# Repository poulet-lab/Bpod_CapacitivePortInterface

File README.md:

# Capacitive Port Interface for Bpod State Machine

A drop-in replacement for the [regular port interface](https://www.sanworks.io/shop/viewproduct?productID=1004) enabling for capacitive sensing of lick events. Connect a metal lickspout with a short piece of wire to the SNS port of the interface. Baseline calibration will be performed upon power-on - it can be triggered by briefly unplugging the port interface's RJ45 cable from the Bpod's behavior port once everything is in place.

## Bill of Materials
| Item     | Vendor    | Qty | Part Number                                                                                                                        | Description                 |
| :------- | :------   | :-: | :--------------------------------------------------------------------------------------------------------------------------------- | :-------------------------  |
| C1       | Digi-Key  |  1  | [CC1206JRX7R9BB682-ND](https://www.digikey.com/products/en?keywords=CC1206JRX7R9BB682-ND)                                                        | 6.8 nF capacitor (1206)      |
| C2, C3   | Digi-Key  |  2  | [311-1179-2-ND](https://www.digikey.com/products/en?keywords=311-1179-2-ND)                                                        | 100 nF capacitor (1206)     |
| IC1      | Digi-Key  |  1  | [AT42QT1011-TSHRTR-ND](https://www.digikey.com/products/en?keywords=AT42QT1011-TSHRTR-ND)                                          | touch sensor IC             |
| R1       | Digi-Key  |  1  | [13-RC1206FR-1010KLTR-ND](https://www.digikey.com/products/en?keywords=13-RC1206FR-1010KLTR-ND)                                    | 10k ohm resistor (1206)     |
| R2       | Digi-Key  |  1  | [13-RC1206FR-1010RLTR-ND](https://www.digikey.com/products/en?keywords=13-RC1206FR-1010RLTR-ND)                                    | 10 ohm resistor (1206)      |
|          | Digi-Key  |  1  | [3362P-501LF-ND](https://www.digikey.com/products/en?keywords=3362P-501LF-ND)                                                      | 500 ohm trimpot             |
|          | Digi-Key  |  1  | [277-1721-ND](https://www.digikey.com/products/en?keywords=277-1721-ND)                                                            | 2 pos screw terminal	    |
|          | Digi-Key  |  1  | [277-1736-ND](https://www.digikey.com/products/en?keywords=277-1736-ND)                                                            | 4 pos screw terminal	    |
|          | Digi-Key  |  1  | [A31413-ND](https://www.digikey.com/products/en?keywords=A31413-ND)                                                                | Ethernet jack               |
|          | Lee Valve |  1  | [LHDA1231115H](https://www.theleeco.com/products/electro-fluidic-systems/solenoid-valves/control-valves/lhd-series/3-port/ported/) | Solenoid valve              |

The above BOM is for the ```no_user``` version of the PCB. If you want to access the 
extra two lines of the RJ45 connector (like we do at Poulet-Lab) use the respective version of the PCB (```PortBreakoutCapacitive_r*.brd```) and swap the 4 position screw terminal for a 6 position screw terminal ([277-1738-ND](https://www.digikey.com/products/en?keywords=277-1738-ND)).

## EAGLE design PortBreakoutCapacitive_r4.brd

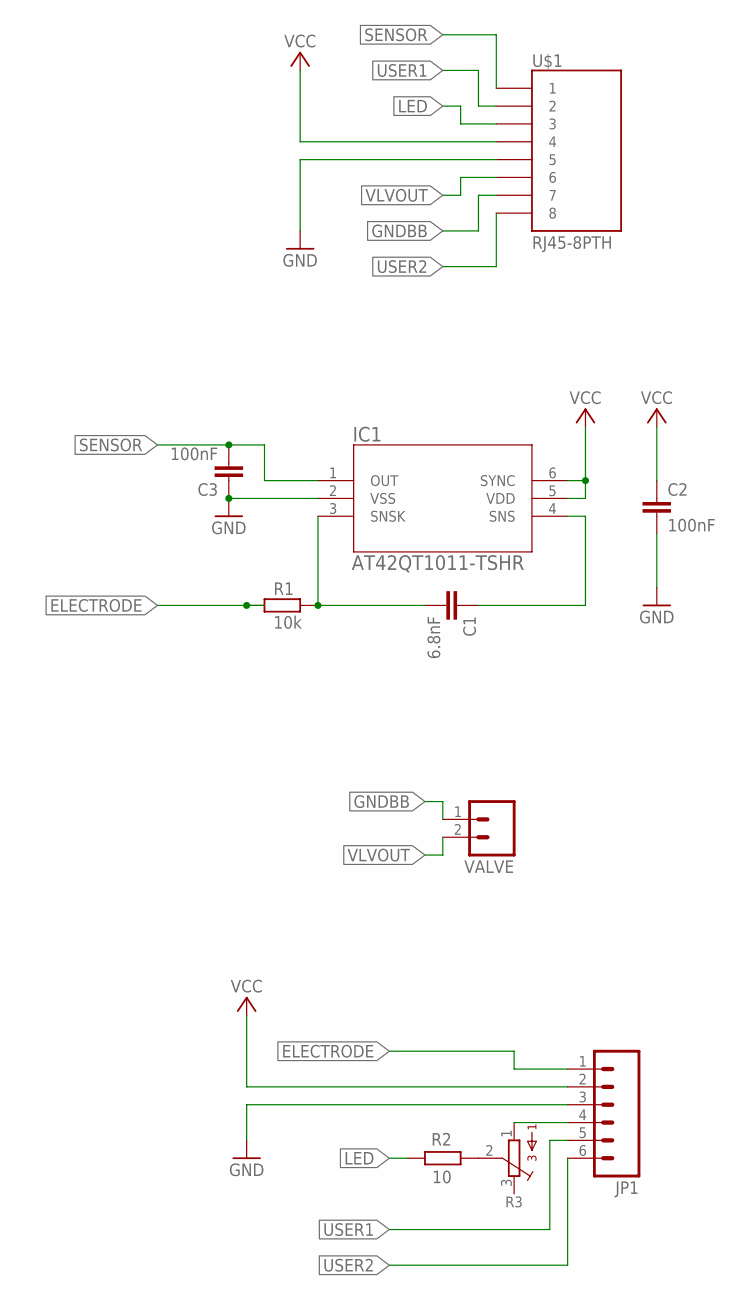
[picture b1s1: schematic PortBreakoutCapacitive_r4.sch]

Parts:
C1: 6.8nF; C1206
C2, C3: 100nF; C1206
IC1: AT42QT1011-TSHR; 6ST1_ATM
JP1: M063.5MM-6; SCREWTERMINAL-3.5MM-6
R1: 10k; R1206
R2: 10; R1206
R3: 3362R
U$1: RJ45-8PTH; RJ45-8
VALVE: M023.5MM_LOCK; SCREWTERMINAL-3.5MM-2_LOCK

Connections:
ELECTRODE: JP1.1, R1.1
GND: C2.2, C3.1, IC1.2 (VSS), JP1.3, U$1.5
GNDBB: U$1.7, VALVE.1
LED: R2.2, U$1.3
unnamed: R2.1, R3.2
unnamed: JP1.4, R3.1
SENSOR: C3.2, IC1.1 (OUT), U$1.1
SNS: C1.1, IC1.4 (SNS)
SNSK: C1.2, IC1.3 (SNSK), R1.2
USER1: JP1.5, U$1.2
USER2: JP1.6, U$1.8
VCC: C2.1, IC1.5 (VDD), IC1.6 (SYNC), JP1.2, U$1.4
VLVOUT: U$1.6, VALVE.2

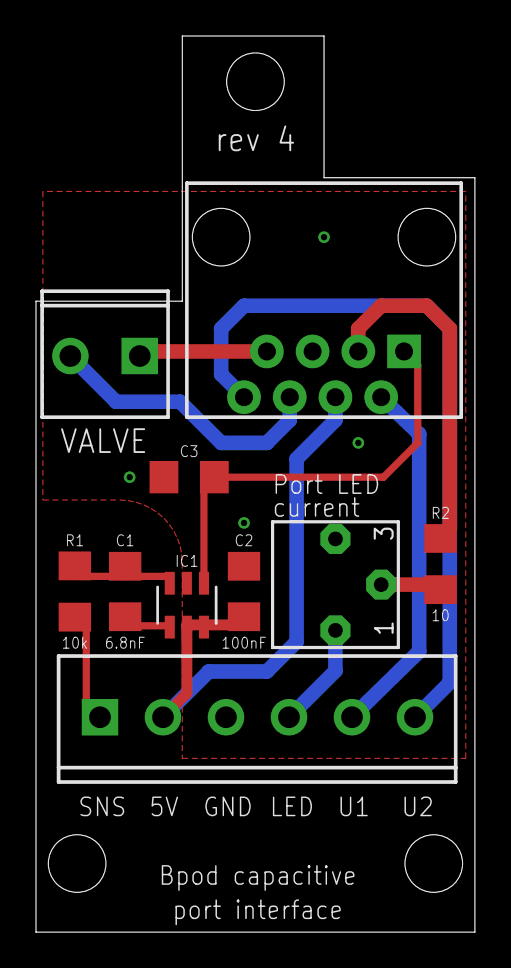
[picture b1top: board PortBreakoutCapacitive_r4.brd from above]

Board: 2 copper layers, 24.4 x 49.8 mm, 10 parts (0 on the bottom side), 13 nets.

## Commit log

2021-04-01 minor adjustments
2021-06-29 revision 2
2022-03-11 Removed transistor Q1
2022-03-11 minor clean-up
2022-03-11 remove autosaves
2022-04-19 rev 4: C1 with lower capacitance
2022-04-19 Revert "rev 4: C1 with lower capacitance"
    This reverts commit f0b3ebc7fd996792bcba9bfe078b693bdcbdf926.
2022-04-19 some changes to trace routing
2022-12-02 added label "The Poulet Lab" to backside
